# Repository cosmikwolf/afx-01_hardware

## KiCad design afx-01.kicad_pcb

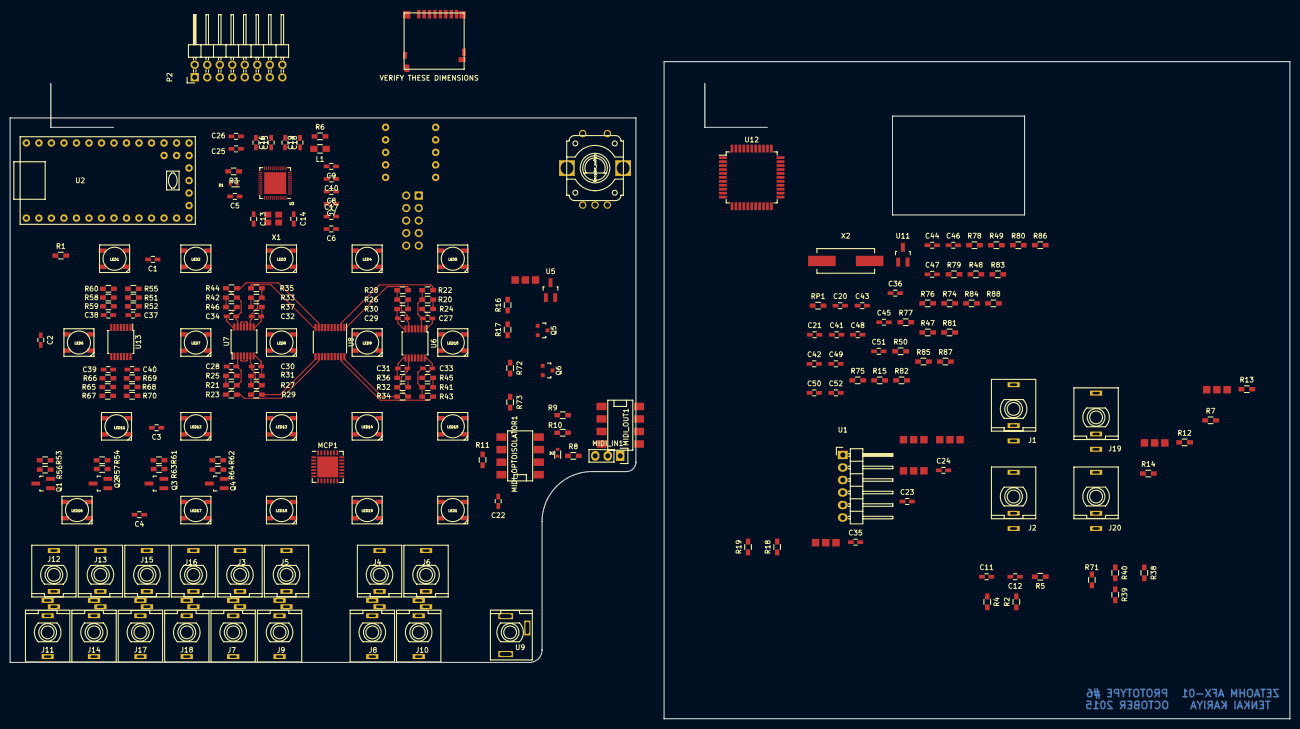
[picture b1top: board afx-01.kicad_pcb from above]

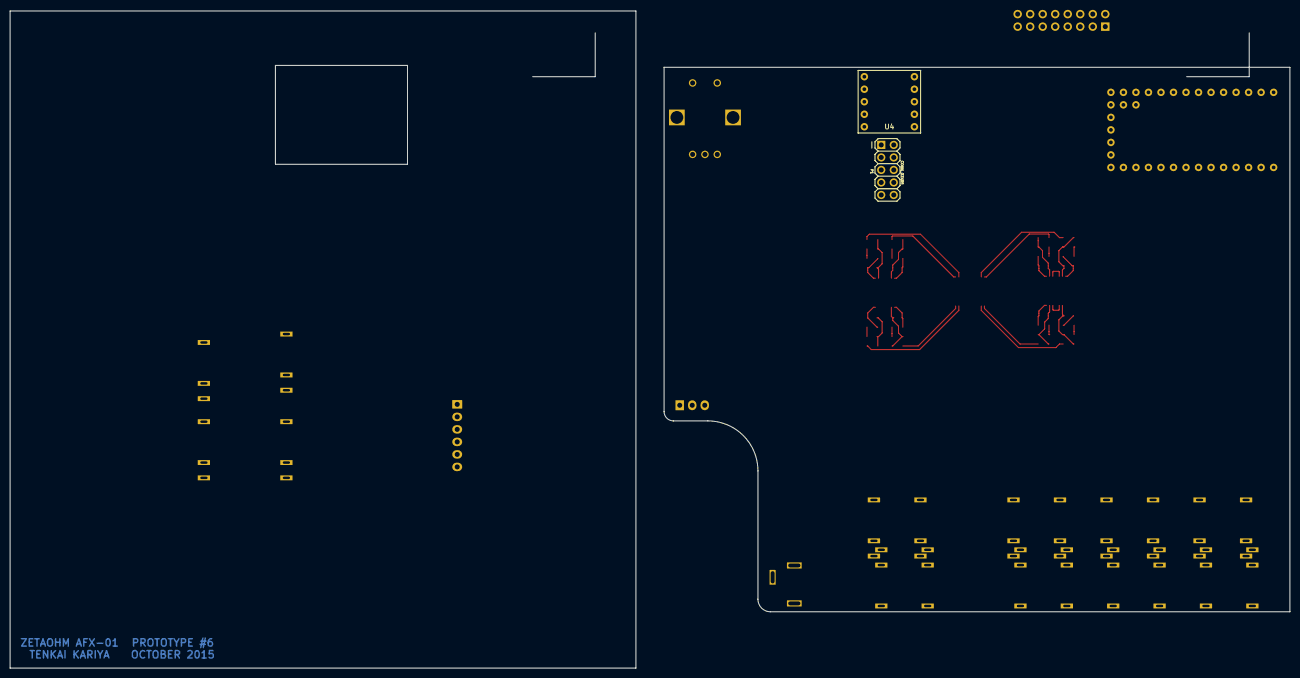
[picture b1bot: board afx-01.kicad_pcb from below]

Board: 2 copper layers, 259.7 x 133.3 mm, 219 parts (2 on the bottom side), 156 nets.

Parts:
C1, C2, C3, C4: 100uf; C_0603_HandSoldering
C5: 1µfT; C_0603_HandSoldering
C6, C7, C8, C9, C10, C15, C18, C26: 100nF; C_0603_HandSoldering
C11, C12: 100µfT; C_0603_HandSoldering
C13, C14: 22pF; C_0603_HandSoldering
C16, C17, C19: 10µfT; C_0603_HandSoldering
C20, C21: .01µf; C_0603_HandSoldering
C22: 100µf; C_0603_HandSoldering
C23, C24, C35, C36, C41, C42, C43, C44: 0.1uf; C_0603_HandSoldering
C25: 4.7µfT; C_0603_HandSoldering
C27, C28, C29, C30, C31, C32, C33, C34: 1nf; C_0603_HandSoldering
C37, C38, C39, C40: 3.3nf; C_0603_HandSoldering
C45, C47, C49, C50, C51, C52: 4.7nf; C_0603_HandSoldering
C46, C48: 18pf; C_0603_HandSoldering
D1: LL4148; SOD-523
D2: 1A; SOD-523
ENC1: Encoder_switch; AB2_ROTARY_ENCODER_W_SWITCH
J1, J2, J3, J4, J5, J6, J7, J8, J9, J10, J11, J12, J13, J14, J15, J16, J17, J18, J19, J20: Mono_AudioConnector; THONKICONN
JP1, JP2, JP3, JP4, JP5, JP6, JP7: JUMPER3; Jumper_3way
L1: 742792093; C_0805_HandSoldering
LED1, LED1#2, LED2, LED3, LED4, LED5, LED6, LED7, LED8, LED9, LED10, LED11, LED12, LED13, LED14, LED15, LED16, LED17, LED18, LED19: WS2812b; WS2812b_SMD
MCP1: MCP23017-QFN; QFN-28-1EP_6x6mm_Pitch0.65mm
MIDI_IN1: MIDI_CONN_FEMALE; MIDI_Wire_Connector
MIDI_OPTOISOLATOR1: 6N139; DIP-8_SMD
MIDI_OUT1: MIDI_CONN_FEMALE; DIP-8_SMD
P1: CONN_02X05; AB2_HDR_M05-2V
P2: CONN_02X08; Pin_Header_Angled_2x08
Q1, Q2, Q3, Q4: BSS138; SOT-23_Handsoldering
Q5, Q6: BSS138; SOT-23
R1: 500; R_0603_HandSoldering
R2, R8, R9, R10, R11: 220; R_0603_HandSoldering
R3, R53, R54, R61, R62, R71: 10k; R_0603_HandSoldering
R4, R5, R39: 47k; R_0603_HandSoldering
R6: 0; R_0603_HandSoldering
R7, R12, R13, R14, R15, R24, R25, R30, R31, R36, R37, R45, R46, R47, R48, R49, R50, R74, R75, R76, R77, R78, R79, R80, R81, R82: 1k; R_0603_HandSoldering
R16, R17, R18, R19, R72, R73: 4.7k; R_0603_HandSoldering
R20, R21, R26, R27, R32, R33, R41, R42, R56, R57, R63, R64: 100k; R_0603_HandSoldering
R22, R23, R28, R29, R34, R35, R43, R44: 50k; R_0603_HandSoldering
R38: 82k; R_0603_HandSoldering
R40: 220k; R_0603_HandSoldering
R51, R58, R65, R68: 242; R_0603_HandSoldering
R52, R59, R66, R69: 33k; R_0603_HandSoldering
R55, R60, R67, R70: 200k; R_0603_HandSoldering
R83, R84, R85, R86, R87, R88: 470k; R_0603_HandSoldering
RP1: 10k; R_0603_HandSoldering
U1: ADA_SSD1306_I2C; Pin_Header_Angled_1x06
U2: Teensy_3.1; Teensy3.1_Min_I2C2
U3: SAM2695; UQFN-48-1EP_6x6mm_Pitch0.4mm
U4: MicroSD_Adapter; MicroSD
U5, U11: MCP1703; SOT-23_Handsoldering
U6, U7: OPA4171; TSSOP-14_4.4x5mm_Pitch0.65mm
U8: AD5676; TSSOP-20_4.4x6.5mm_Pitch0.65mm
U9: 3_pin_stereo; KOBICONN_ST
U10: MicroSD_Connector; AMPHENOL_MICROSD
U12: QT1481; LQFP-44_10x10mm_Pitch0.8mm
U13: MCP6004; TSSOP-14_4.4x5mm_Pitch0.65mm
X1: 12MHz; Xtal_3.2mm
X2: 16Mhz; Crystal_HC49-SD_SMD

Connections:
+3V3: C1.1, C2.1, C3.1, C4.1, C6.2, C7.2, C8.2, C9.2, C10.2, C17.1, C18.2, C19.1, D1.2, L1.1, L1.2, LED1.2, LED1#2.2, LED2.2, LED3.2, LED4.2, LED5.2, LED6.2, LED7.2, LED8.2, LED9.2, LED10.2, LED11.2, LED12.2, LED13.2, LED14.2, LED15.2, LED16.2, LED17.2, LED18.2, LED19.2, P1.3, Q5.1, R3.1, R16.2, R17.2, R18.2, R19.2, R53.1, R54.1, R61.1, R62.1, R71.1, U2.44, U2.48, U3.6, U3.8, U3.11, U3.12, U3.20, U3.31, U3.35, U3.41, U3.46, U3.47, U8.4, U8.14, U13.4
+5V: C43.2, JP3.2, MCP1.5, MCP1.11, MCP1.14, P1.5, R38.1, R72.2, R73.2, U2.46, U4.7, U8.3, U8.18, U11.3
CV_IN1: C37.2, R52.2, U2.23, U13.1
CV_IN2: C38.2, R59.2, U2.22, U13.7
CV_IN3: C39.2, R66.2, U2.21, U13.8
CV_IN4: C40.2, R69.2, U2.20, U13.14
DAC0: R22.1, U8.2
DAC1: R28.1, U8.1
DAC2: R34.1, U8.20
DAC3: R43.1, U8.19
DAC4: R23.1, U8.12
DAC5: R29.1, U8.11
DAC6: R35.1, U8.10
DAC7: R44.1, U8.9
DAC_CS: U2.3, U8.5
DAC_SDO: P1.7, U8.16
DISP_RESET: U1.4, U2.5
ENC1A: C20.1, RP1.1, U2.17
ENC1B: C21.1, U2.16
ENC1SW: ENC1.4, MCP1.25
GATE_IN3: JP4.1, JP4.2, JP6.1, JP6.2, Q3.2, R61.2, U2.14
GATE_IN4: JP5.1, JP5.2, JP7.1, JP7.2, Q4.2, R62.2, U2.15
GATE_OUT1: MCP1.21, R7.2
GATE_OUT2: MCP1.22, R12.2
GATE_OUT3: MCP1.23, R13.2
GATE_OUT4: MCP1.24, R14.2
GND: C1.2, C2.2, C3.2, C4.2, C20.2, C21.2, C22.2, C23.1, C24.2, C35.2, C36.2, C41.2, C42.2, C43.1, C44.1, C46.2, C48.2, ENC1.2, ENC1.5, J1.1, J2.1, J3.1, J4.1, J5.1, J6.1, J7.1, J8.1, J9.1, J10.1, J11.1, J12.1, J13.1, J14.1, J15.1, J16.1, J17.1, J18.1, J19.1, J20.1, LED1.3, LED1#2.3, LED2.3, LED3.3, LED4.3, LED5.3, LED6.3, LED7.3, LED8.3, LED9.3, LED10.3, LED11.3, LED12.3, LED13.3, LED14.3, LED15.3, LED16.3, LED17.3, LED18.3, LED19.3, MCP1.6, MCP1.12, MCP1.13, MIDI_IN1.2, MIDI_OPTOISOLATOR1.5, MIDI_OUT1.2, P1.1, P2.3, P2.4, P2.5, P2.6, P2.7, P2.8, Q1.3, Q2.3, Q3.3, Q4.3, R39.2, R40.2, U2.43, U2.49, U4.1, U5.1, U8.13, U8.15, U11.1, U12.18, U12.28, U12.39, U12.42, U13.3, U13.5, U13.10, U13.11, U13.12
GNDA: C5.2, C6.1, C7.1, C8.1, C9.1, C10.1, C13.2, C14.2, C15.1, C16.2, C17.2, C18.1, C19.2, C25.2, C26.1, R4.2, R5.2, R6.1, R6.2, U2.47, U3.4, U3.9, U3.10, U3.13, U3.14, U3.15, U3.18, U3.25, U3.36, U3.37, U3.45, U3.48, U9.1
LED_DIN: R1.2, U2.6
MCP_GATE_IN1: MCP1.17, Q1.2, R53.2
MCP_GATE_IN2: MCP1.18, Q2.2, R54.2
MCP_GATE_IN3: JP4.3, JP6.3, MCP1.19
MCP_GATE_IN4: JP5.3, JP7.3, MCP1.20
MIDI_IN_EXTERNAL: MIDI_OPTOISOLATOR1.6, R11.2, U2.7
MIDI_OUT_EXTERNAL: R2.2, R10.1, U2.8
MISO: P1.10, U2.12, U4.5, U12.2
MOSI: P1.8, U2.11, U4.4, U8.7, U12.1
unnamed: C5.1, D1.1, R3.2, U3.38
unnamed: C11.1, U3.2
unnamed: C11.2, R4.1, U9.3
unnamed: C12.1, U3.1
unnamed: C12.2, R5.1, U9.2
unnamed: C13.1, U3.39, X1.1
unnamed: C14.1, U3.40, X1.3
unnamed: C15.2, C16.1, U3.5
unnamed: C23.2, JP3.3, P2.11, P2.12
unnamed: C24.1, JP3.1, U5.2
unnamed: C25.1, C26.2, U3.34
unnamed: C27.1, R24.1, U6.1
unnamed: C27.2, R20.1, R22.2, U6.2
unnamed: C28.1, R25.1, U7.1
unnamed: C28.2, R21.1, R23.2, U7.2
unnamed: C29.1, R30.1, U6.7
unnamed: C29.2, R26.1, R28.2, U6.6
unnamed: C30.1, R31.1, U7.7
unnamed: C30.2, R27.1, R29.2, U7.6
unnamed: C31.1, R36.1, U6.8
unnamed: C31.2, R32.1, R34.2, U6.9
unnamed: C32.1, R37.1, U7.8
unnamed: C32.2, R33.1, R35.2, U7.9
unnamed: C33.1, R45.1, U6.14
unnamed: C33.2, R41.1, R43.2, U6.13
unnamed: C34.1, R46.1, U7.14
unnamed: C34.2, R42.1, R44.2, U7.13
unnamed: C36.1, C41.1, C42.1, C44.2, U11.2, U12.4, U12.5, U12.17, U12.27, U12.29, U12.38
unnamed: C37.1, R51.2, R52.1, R55.2, U13.2
unnamed: C38.1, R58.2, R59.1, R60.2, U13.6
unnamed: C39.1, R65.2, R66.1, R67.2, U13.9
unnamed: C40.1, R68.2, R69.1, R70.2, U13.13
unnamed: C45.1, R77.2, U12.16
unnamed: C45.2, R88.2, U12.30
unnamed: C46.1, U12.8, X2.1
unnamed: C47.1, R78.2, U12.15
unnamed: C47.2, R87.2, U12.31
unnamed: C48.1, U12.7
unnamed: C49.1, R79.2, U12.14
unnamed: C49.2, R86.2, U12.32
unnamed: C50.1, R80.2, U12.13
unnamed: C50.2, R85.2, U12.33
unnamed: C51.1, R81.2, U12.34
unnamed: C51.2, R84.2, U12.35
unnamed: C52.2, R83.2, U12.37
unnamed: D2.1, MIDI_IN1.5, MIDI_OPTOISOLATOR1.3
unnamed: D2.2, MIDI_OPTOISOLATOR1.2, R8.1
unnamed: J1.2, J1.3, R7.1
unnamed: J2.2, J2.3, R12.1
unnamed: J3.2, J3.3, R20.2, R24.2
unnamed: J4.2, J4.3, R21.2, R25.2
unnamed: J5.2, J5.3, R26.2, R30.2
unnamed: J6.2, J6.3, R27.2, R31.2
unnamed: J7.2, J7.3, R32.2, R36.2
unnamed: J8.2, J8.3, R33.2, R37.2
unnamed: J9.2, J9.3, R41.2, R45.2
unnamed: J10.2, J10.3, R42.2, R46.2
unnamed: J11.2, J11.3, R55.1
unnamed: J12.2, J12.3, R56.1
unnamed: J13.2, J13.3, R57.1
unnamed: J14.2, J14.3, R60.1
unnamed: J15.2, J15.3, R63.1
unnamed: J16.2, J16.3, R64.1
unnamed: J17.2, J17.3, R67.1
unnamed: J18.2, J18.3, R70.1
unnamed: J19.2, J19.3, R13.1
unnamed: J20.2, J20.3, R14.1
unnamed: JP1.2, U1.1
unnamed: JP2.2, U1.2
unnamed: LED1.1, LED1#2.1, LED17.1, LED18.1, LED19.1, R1.1
unnamed: LED1.4, LED1#2.4, LED2.1, LED17.4, LED18.4, LED19.4
unnamed: LED2.4, LED3.1
unnamed: LED3.4, LED4.1
unnamed: LED4.4, LED5.1
unnamed: LED5.4, LED6.1
unnamed: LED6.4, LED7.1
unnamed: LED7.4, LED8.1
unnamed: LED8.4, LED9.1
unnamed: LED9.4, LED10.1
unnamed: LED10.4, LED11.1
unnamed: LED11.4, LED12.1
unnamed: LED12.4, LED13.1
unnamed: LED13.4, LED14.1
unnamed: LED14.4, LED15.1
unnamed: LED15.4, LED16.1
unnamed: MIDI_IN1.4, R8.2
unnamed: MIDI_OUT1.4, R9.2
unnamed: MIDI_OUT1.5, R10.2
unnamed: Q1.1, R56.2
unnamed: Q2.1, R57.2
unnamed: Q3.1, R63.2
unnamed: Q4.1, R64.2
unnamed: R2.1, U3.16
unnamed: R15.2, U12.19
unnamed: R47.2, U12.20
unnamed: R48.2, U12.21
unnamed: R49.2, U12.22
unnamed: R50.2, U12.23
unnamed: R71.2, U8.17
unnamed: R74.2, U12.24
unnamed: R75.2, U12.25
unnamed: R76.2, U12.26
unnamed: R82.2, U12.36
unnamed: R83.1, R84.1, R85.1, R86.1, R87.1, R88.1, U12.12
QT_CS: U2.41, U12.44
QT_RX: U2.10, U12.9
QT_TX: U2.9, U12.10
SCL0: JP2.1, P1.2, Q6.2, R17.1, U2.19
SCL0_5v: MCP1.8, Q5.3, R72.1
SCL1: JP2.3, R19.1, U2.29
SCLK: P1.6, U2.13, U4.3, U8.6
SDA0: JP1.1, P1.4, Q5.2, R16.1, U2.18
SDA0_5v: MCP1.9, Q6.3, R73.1
SDA1: JP1.3, R18.1, U2.30
SD_CS: U2.2, U4.2, U10.2
VCC: C22.1, MIDI_OPTOISOLATOR1.8, R9.1, R11.1, RP1.2
VDD: C35.1, P2.1, P2.2, U5.3, U6.4
VREF_OPA: R38.2, R39.1, R40.1, U6.3, U6.5, U6.10, U6.12, U7.3, U7.5, U7.10, U7.12
VSS: P2.9, P2.10, R51.1, R58.1, R65.1, R68.1, U6.11

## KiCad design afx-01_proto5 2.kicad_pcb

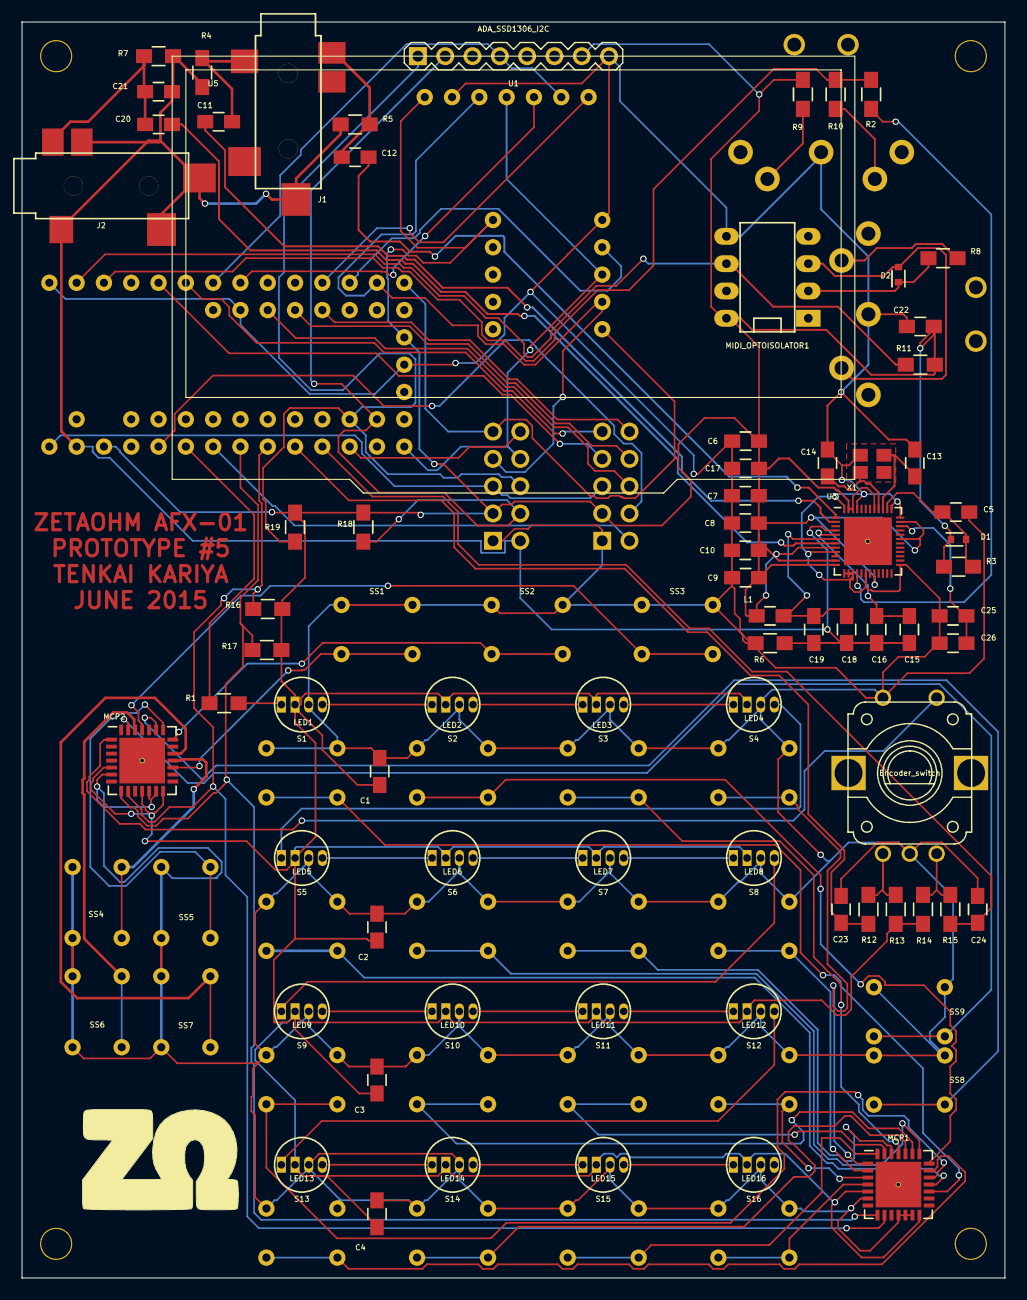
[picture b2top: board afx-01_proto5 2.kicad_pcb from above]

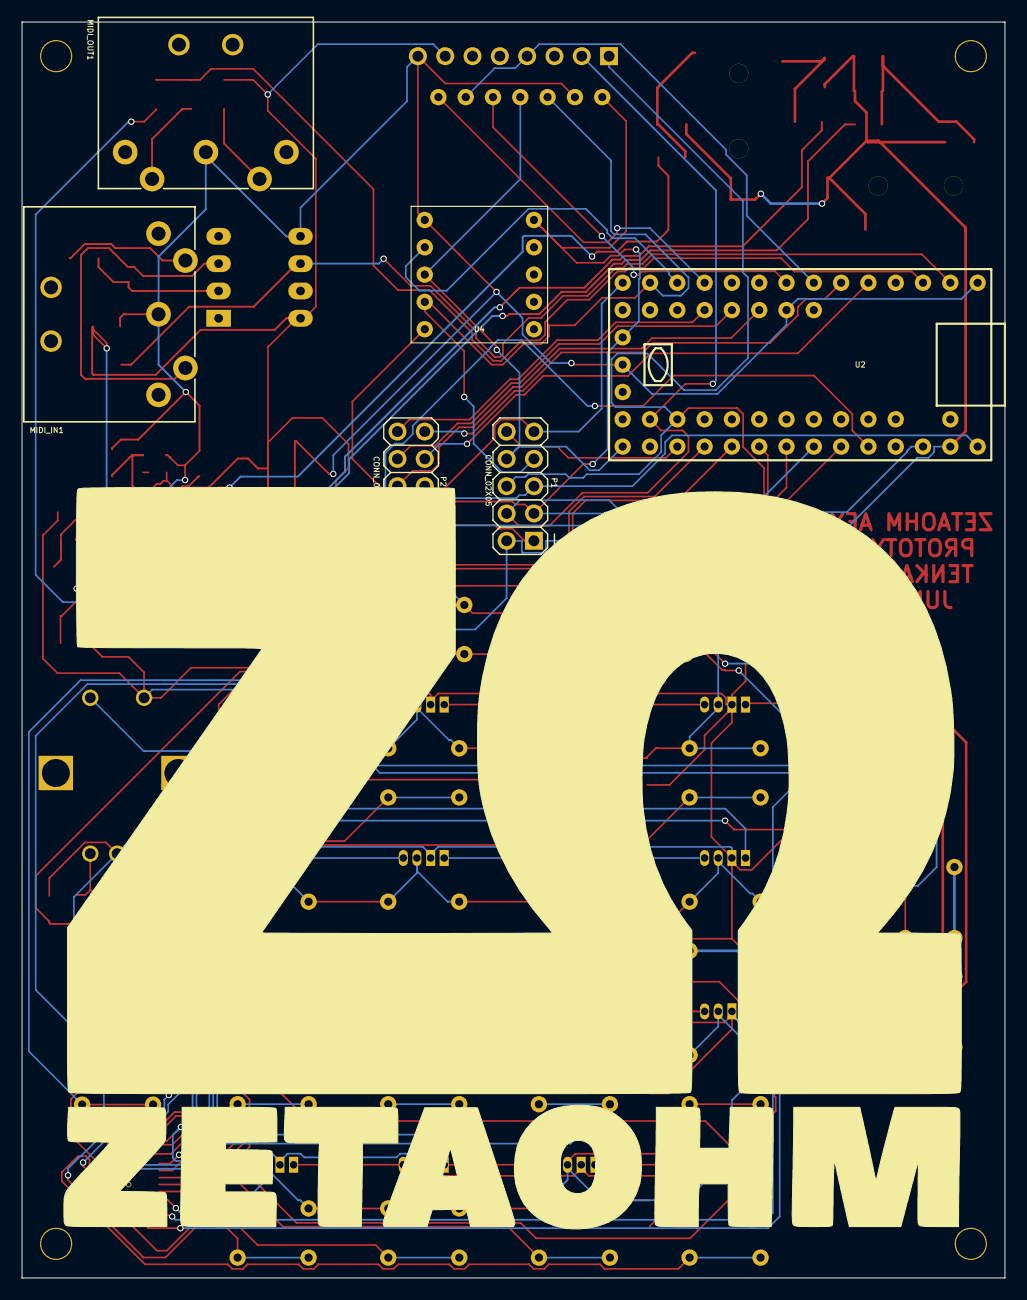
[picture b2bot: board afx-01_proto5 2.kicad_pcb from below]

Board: 2 copper layers, 91.4 x 116.8 mm, 105 parts (6 on the bottom side), 89 nets.

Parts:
C1, C2, C3, C4, C22: 100µf; C_0805_HandSoldering
C5, C20: 1µfT; C_0805_HandSoldering
C6, C7, C8, C9, C10, C15, C18, C26: 100nF; C_0805_HandSoldering
C11, C12: 100µfT; C_0805_HandSoldering
C13, C14: 22pF; C_0805_HandSoldering
C16, C17, C19: 10µfT; C_0805_HandSoldering
C21: 220pF; C_0805_HandSoldering
C23, C24: .01µf; C_0805_HandSoldering
C25: 4.7µfT; C_0805_HandSoldering
D1: LL4148; SOD-523
D2: 1A; SOD-523
ENC1: Encoder_switch; AB2_ROTARY_ENCODER_W_SWITCH
J1: HeadphoneOut; Switchcraft_3.5mm_SMD_Stereo
J2: MicIn; Switchcraft_3.5mm_SMD_Stereo
L1: 742792093; C_0805_HandSoldering
LED1, LED2, LED3, LED4, LED5, LED6, LED7, LED8, LED9, LED10, LED11, LED12, LED13, LED14, LED15, LED16: WS2812b; WS2811_5mm_ThroughHole
MCP1, MCP2: MCP23017-QFN; QFN-28-1EP_6x6mm_Pitch0.65mm
MIDI_IN1: MIDI_CONN_FEMALE; SDS-50J
MIDI_OPTOISOLATOR1: 6N139; DIP-8__300_ELL
MIDI_OUT1: MIDI_CONN_FEMALE; SDS-50J
P1, P2: CONN_02X05; AB2_HDR_M05-2V
R1: 500; R_0805_HandSoldering
R2, R8, R9, R10, R11: 220; R_0805_HandSoldering
R3, R12, R13, R14, R15: 10k; R_0805_HandSoldering
R4, R5: 47k; R_0805_HandSoldering
R6: 0; R_0805_HandSoldering
R7, R16, R17, R18, R19: 4.7k; R_0805_HandSoldering
S1, S2, S3, S4, S5, S6, S7, S8, S9, S10, S11, S12, S13, S14, S15, S16: DPST_Switch; B3F-1050_6mm_Switch
SS1, SS2, SS3, SS4, SS5, SS6, SS7, SS8, SS9: DPST_Switch; B3F-1050_6mm_Switch
U1: ADA_SSD1306_I2C; AB2_HDR_M08-1V
U2: Teensy_3.1; Teensy3.1
U3: SAM2695; UQFN-48-1EP_6x6mm_Pitch0.4mm
U4: MicroSD_Adapter; MicroSD
U5: SSD1306; SSD1306_XL
X1: 12MHz; Xtal_3.2mm

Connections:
/3: P2.7, U2.3
/4: P2.9, U2.4
/5: U1.4, U2.5, U5.6
/6: U2.6, U5.5
/9: U2.9, U5.7
/10: U2.10, U4.2
/11: P1.7, U2.11, U4.4, U5.3
/12: P1.9, U2.12, U4.5
/13: P1.8, U2.13, U4.3, U5.4
/15: P1.10, U2.15
/20: P2.2, U2.20
/22: P2.4, U2.22
/24: P2.6, U2.24
/25: P2.8, U2.25
/26: P2.10, U2.26
/29: P1.4, R18.1, U1.2, U2.29
/30: P1.6, R19.1, U1.1, U2.30
/LED Matrix/LED_DIN: R1.2, U2.21
/MidiConnectors/RX: MIDI_OPTOISOLATOR1.6, R11.2, U2.0
/SoundBoard/MIDIIN: R2.2, R10.1, U2.1
/SwitchMatrix/ENCA: C23.1, R12.2, U2.17
/SwitchMatrix/ENCB: C24.1, R15.2, U2.16
/SwitchMatrix/SCL: MCP1.8, MCP2.8, R17.2, U2.19
/SwitchMatrix/SDA: MCP1.9, MCP2.9, R16.2, U2.18
/VIN: P1.5, P2.5, U2.46
AGND: C15.1, C16.2, C18.1, C19.2, C21.1, J1.5, J2.1, J2.2, J2.3, J2.5, P1.2, R4.2, R5.2, R6.1, R7.2, U2.47, U3.4
GND: C1.2, C2.2, C3.2, C4.2, C5.2, C6.1, C7.1, C8.1, C9.1, C10.1, C13.2, C14.2, C17.2, C22.2, C23.2, C24.2, C25.2, C26.1, ENC1.2, ENC1.5, LED1.3, LED2.3, LED3.3, LED4.3, LED5.3, LED6.3, LED7.3, LED8.3, LED9.3, LED10.3, LED11.3, LED12.3, LED13.3, LED14.3, LED15.3, LED16.3, MCP1.6, MCP1.11, MCP1.12, MCP1.13, MCP2.6, MCP2.12, MCP2.13, MIDI_IN1.2, MIDI_OPTOISOLATOR1.5, MIDI_OUT1.2, P1.1, P2.1, R6.2, S1.3, S1.4, S2.3, S2.4, S3.3, S3.4, S4.3, S4.4, S5.3, S5.4, S6.3, S6.4, S7.3, S7.4, S8.3, S8.4, S9.3, S9.4, S10.3, S10.4, S11.3, S11.4, S12.3, S12.4, S13.3, S13.4, S14.3, S14.4, S15.3, S15.4, S16.3, S16.4, SS1.3, SS1.4, SS2.3, SS2.4, SS3.3, SS3.4, SS4.3, SS4.4, SS5.3, SS5.4, SS6.3, SS6.4, SS7.3, SS7.4, SS8.3, SS8.4, SS9.3, SS9.4, U1.8, U2.43, U2.49, U2.50, U3.9, U3.10, U3.13, U3.14, U3.15, U3.18, U3.25, U3.36, U3.37, U3.45, U3.48, U4.1, U5.2, X1.2
unnamed: C5.1, D1.1, R3.2, U3.38
unnamed: C11.1, U3.2
unnamed: C11.2, J1.1, R4.1
unnamed: C12.1, U3.1
unnamed: C12.2, J1.4, R5.1
unnamed: C13.1, U3.39, X1.1
unnamed: C14.1, U3.40, X1.3
unnamed: C15.2, C16.1, U3.5
unnamed: C20.1, U3.7
unnamed: C20.2, C21.2, J2.4, R7.1
unnamed: C25.1, C26.2, U3.34
unnamed: D2.1, MIDI_IN1.5, MIDI_OPTOISOLATOR1.3
unnamed: D2.2, MIDI_OPTOISOLATOR1.2, R8.1
unnamed: ENC1.1, R12.1, R13.1
unnamed: ENC1.3, R14.1, R15.1
unnamed: ENC1.4, MCP2.1
unnamed: LED1.1, R1.1
unnamed: LED1.4, LED2.1
unnamed: LED2.4, LED3.1
unnamed: LED3.4, LED4.1
unnamed: LED4.4, LED5.1
unnamed: LED5.4, LED6.1
unnamed: LED6.4, LED7.1
unnamed: LED7.4, LED8.1
unnamed: LED8.4, LED9.1
unnamed: LED9.4, LED10.1
unnamed: LED10.4, LED11.1
unnamed: LED11.4, LED12.1
unnamed: LED12.4, LED13.1
unnamed: LED13.4, LED14.1
unnamed: LED14.4, LED15.1
unnamed: LED15.4, LED16.1
unnamed: MCP1.1, S4.1, S4.2
unnamed: MCP1.2, S8.1, S8.2
unnamed: MCP1.3, S12.1, S12.2
unnamed: MCP1.4, S16.1, S16.2
unnamed: MCP1.17, S1.1, S1.2
unnamed: MCP1.18, S5.1, S5.2
unnamed: MCP1.19, S9.1, S9.2
unnamed: MCP1.20, S13.1, S13.2
unnamed: MCP1.21, S2.1, S2.2
unnamed: MCP1.22, S6.1, S6.2
unnamed: MCP1.23, S10.1, S10.2
unnamed: MCP1.24, S14.1, S14.2
unnamed: MCP1.25, S3.1, S3.2
unnamed: MCP1.26, S7.1, S7.2
unnamed: MCP1.27, S11.1, S11.2
unnamed: MCP1.28, S15.1, S15.2
unnamed: MCP2.17, SS1.1, SS1.2
unnamed: MCP2.18, SS4.1, SS4.2
unnamed: MCP2.19, SS7.1, SS7.2
unnamed: MCP2.21, SS2.1, SS2.2
unnamed: MCP2.22, SS5.1, SS5.2
unnamed: MCP2.23, SS8.1, SS8.2
unnamed: MCP2.25, SS3.1, SS3.2
unnamed: MCP2.26, SS6.1, SS6.2
unnamed: MCP2.27, SS9.1, SS9.2
unnamed: MIDI_IN1.4, R8.2
unnamed: MIDI_OUT1.4, R9.2
unnamed: MIDI_OUT1.5, R10.2
unnamed: R2.1, U3.16
VCC: C1.1, C2.1, C3.1, C4.1, C6.2, C7.2, C8.2, C9.2, C10.2, C17.1, C18.2, C19.1, C22.1, D1.2, L1.1, L1.2, LED1.2, LED2.2, LED3.2, LED4.2, LED5.2, LED6.2, LED7.2, LED8.2, LED9.2, LED10.2, LED11.2, LED12.2, LED13.2, LED14.2, LED15.2, LED16.2, MCP1.5, MCP1.14, MCP2.5, MCP2.11, MCP2.14, MIDI_OPTOISOLATOR1.8, P1.3, P2.3, R3.1, R9.1, R11.1, R13.2, R14.2, R16.1, R17.1, R18.2, R19.2, U1.7, U2.44, U2.48, U3.6, U3.8, U3.11, U3.12, U3.20, U3.31, U3.35, U3.41, U3.46, U3.47, U4.7, U5.1

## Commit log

2015-09-22 Moving on to proto6!
2015-10-15 BIG UPDATE! omg so big
    New boards and other things.. jeesh it sbeen too long since the last update
2015-10-17 UPDATEUPDATES!!!
2015-10-22 Added Touch Capacitive Panel
2015-10-22 Adding Layout Files
2015-10-22 Updating Schematics
2015-10-22 Adding Zetaohm.pretty files
2015-10-22 Updating footprints
2015-10-23 Populating pcb file
2015-10-24 UPDATING SCHEMATIC FOR SSD1327
2015-10-26 Small updates
